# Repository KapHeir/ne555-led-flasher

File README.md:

# NE555 LED Flasher PCB

This project is a simple NE555-based LED flasher PCB designed in KiCad.

## Overview

The circuit uses an NE555 timer in astable mode to blink 4 LEDs.  
The flashing speed can be adjusted with a potentiometer.

## Features

- NE555 timer based design
- 4 blinking LEDs
- Adjustable flash rate
- Through-hole components
- 2-layer PCB
- Designed in KiCad

## Power Supply

- Input voltage: 9V

## Main Components

- NE555P
- BC337 transistor
- 4 x LEDs
- 4 x 330 ohm resistors
- 1 x 1k resistor
- 1 x 10k resistor
- 1 x 100k potentiometer
- 1 x 10uF capacitor
- 1 x 100nF capacitor
- 1 x 10nF capacitor
- Terminal input connector
- SPDT switch

## Repository Structure

- `flasor.kicad_pro` — KiCad project file
- `flasor.kicad_sch` — schematic file
- `flasor.kicad_pcb` — PCB layout file
- `Gerbers/` — manufacturing files
- `images/` — project images

## Images

### PCB Layout

### Schematic

### Gerber Preview

## Manufacturing Files

Gerber and drill files are available in the `Gerbers` folder.

## Notes

This is a beginner PCB design project created for learning schematic capture, PCB layout, routing, and manufacturing file generation in KiCad.

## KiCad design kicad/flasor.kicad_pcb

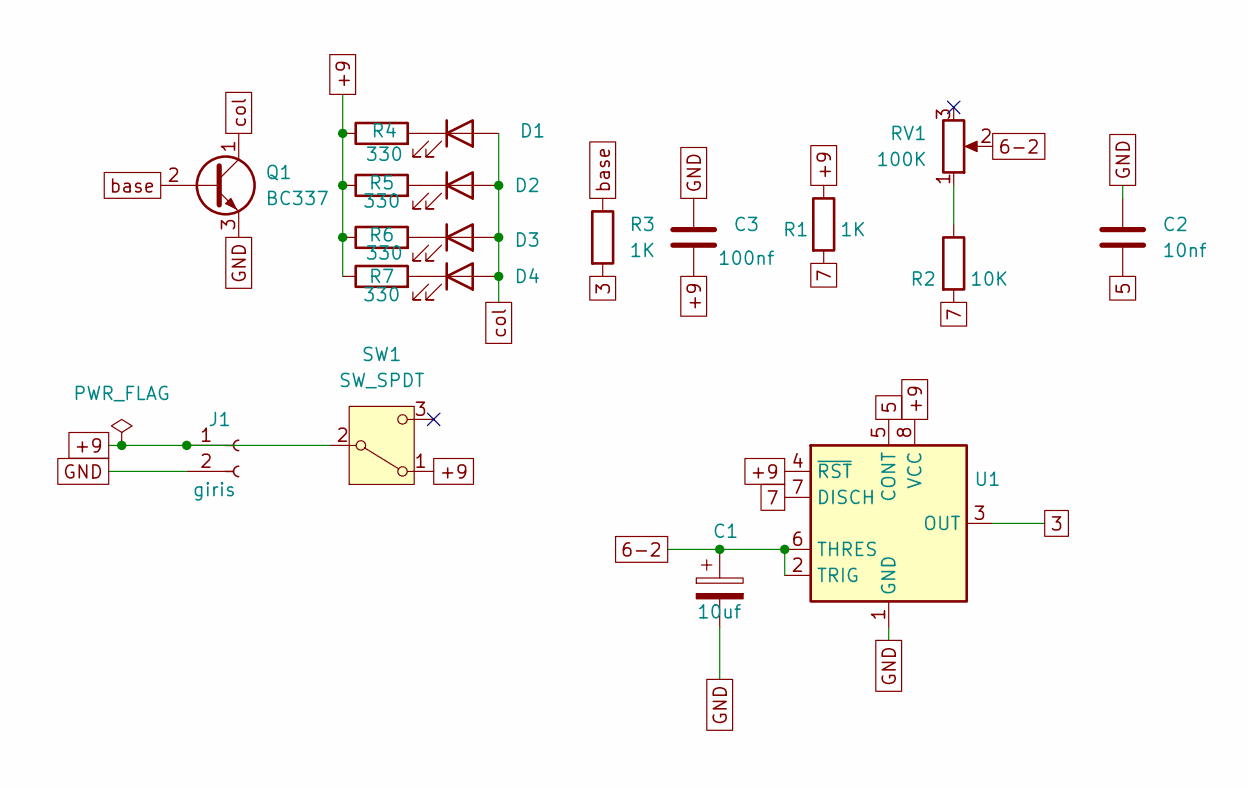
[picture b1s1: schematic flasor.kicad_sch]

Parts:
C1: 10uf; CP_Radial_D5.0mm_P2.00mm
C2: 10nf; C_Disc_D5.0mm_W2.5mm_P2.50mm
C3: 100nf; C_Disc_D5.0mm_W2.5mm_P2.50mm
D1, D2, D3, D4: LED; LED_D5.0mm
J1: giris; BarrelJack_CUI_PJ-102AH_Horizontal
Q1: BC337; TO-92_Inline
R1, R3: 1K; R_Axial_DIN0207_L6.3mm_D2.5mm_P7.62mm_Horizontal
R2: 10K; R_Axial_DIN0207_L6.3mm_D2.5mm_P7.62mm_Horizontal
R4, R5, R6, R7: 330; R_Axial_DIN0207_L6.3mm_D2.5mm_P7.62mm_Horizontal
RV1: 100K; Potentiometer_Bourns_3296W_Vertical
SW1: SW_SPDT; SW_Slide-03_Wuerth-WS-SLTV_10x2.5x6.4_P2.54mm
U1: NE555P; DIP-8_W7.62mm

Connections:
3: R3.2, U1.3 (OUT)
5: C2.2, U1.5 (CONT)
6-2: C1.1, RV1.2, U1.2 (TRIG), U1.6 (THRES)
7: R1.2, R2.2, U1.7 (DISCH)
+9: C3.2, J1.1, R1.1, R4.1, R5.1, R6.1, R7.1, SW1.1 (A), SW1.2 (B), U1.4 (~RST), U1.8 (VCC)
GND: C1.2, C2.1, C3.1, J1.2, Q1.3 (E), U1.1 (GND)
unnamed: D1.1 (K), R4.2
unnamed: D2.1 (K), R5.2
unnamed: D3.1 (K), R6.2
unnamed: D4.1 (K), R7.2
unnamed: R2.1, RV1.1
base: Q1.2 (B), R3.1
col: D1.2 (A), D2.2 (A), D3.2 (A), D4.2 (A), Q1.1 (C)

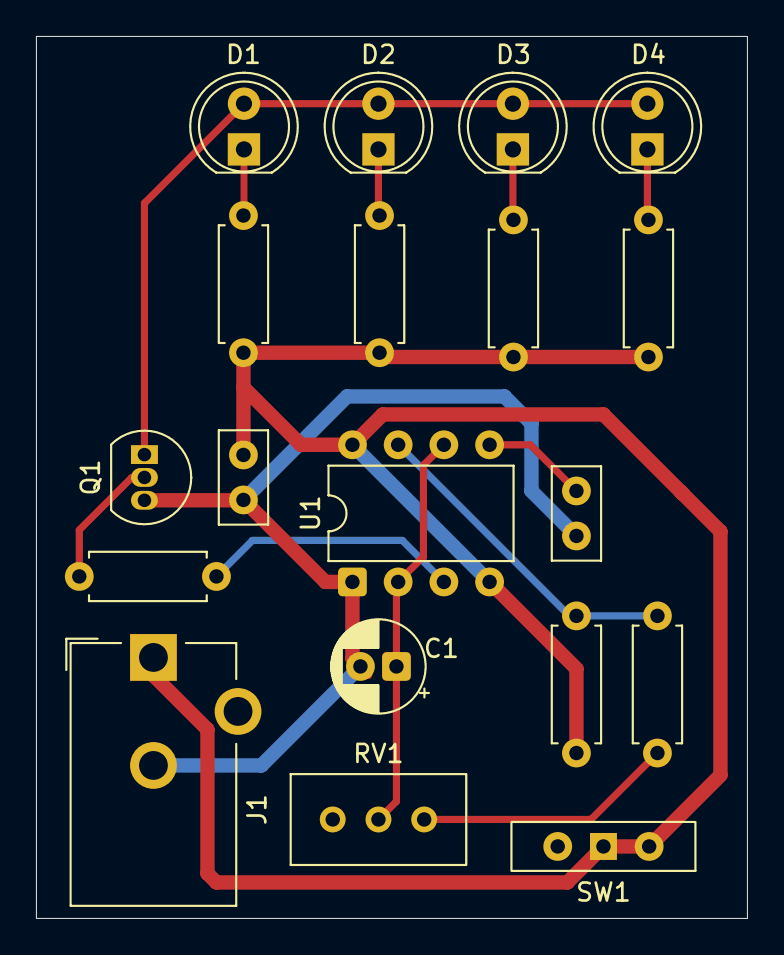
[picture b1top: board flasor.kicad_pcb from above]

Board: 2 copper layers, 39.5 x 49.0 mm, 19 parts (0 on the bottom side), 13 nets.

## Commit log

2026-03-18 Create Gerbers
2026-03-18 Create Placeholder.txt
    Gerber files for manufacturing
2026-03-18 Add files via upload
    upload gerbers files
2026-03-18 Create placeholder.txt
    Project images
2026-03-18 project images
2026-03-18 pcb-layout
2026-03-18 Rename ne555_flasher_sch.png to schematic
2026-03-18 Rename ne555_flasher_gbr.png to gerber-preview
2026-03-18 Rename gerber-preview to gerber-preview.png
2026-03-18 Rename pcb-layout to pcb-layout.png
2026-03-18 Rename schematic to schematic.png
2026-03-18 Create placeholder.txt
    Kicad files
